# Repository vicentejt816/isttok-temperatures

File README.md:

# isttok-temperatures
projeto para medir temperaturas no tokamak ISTTOK

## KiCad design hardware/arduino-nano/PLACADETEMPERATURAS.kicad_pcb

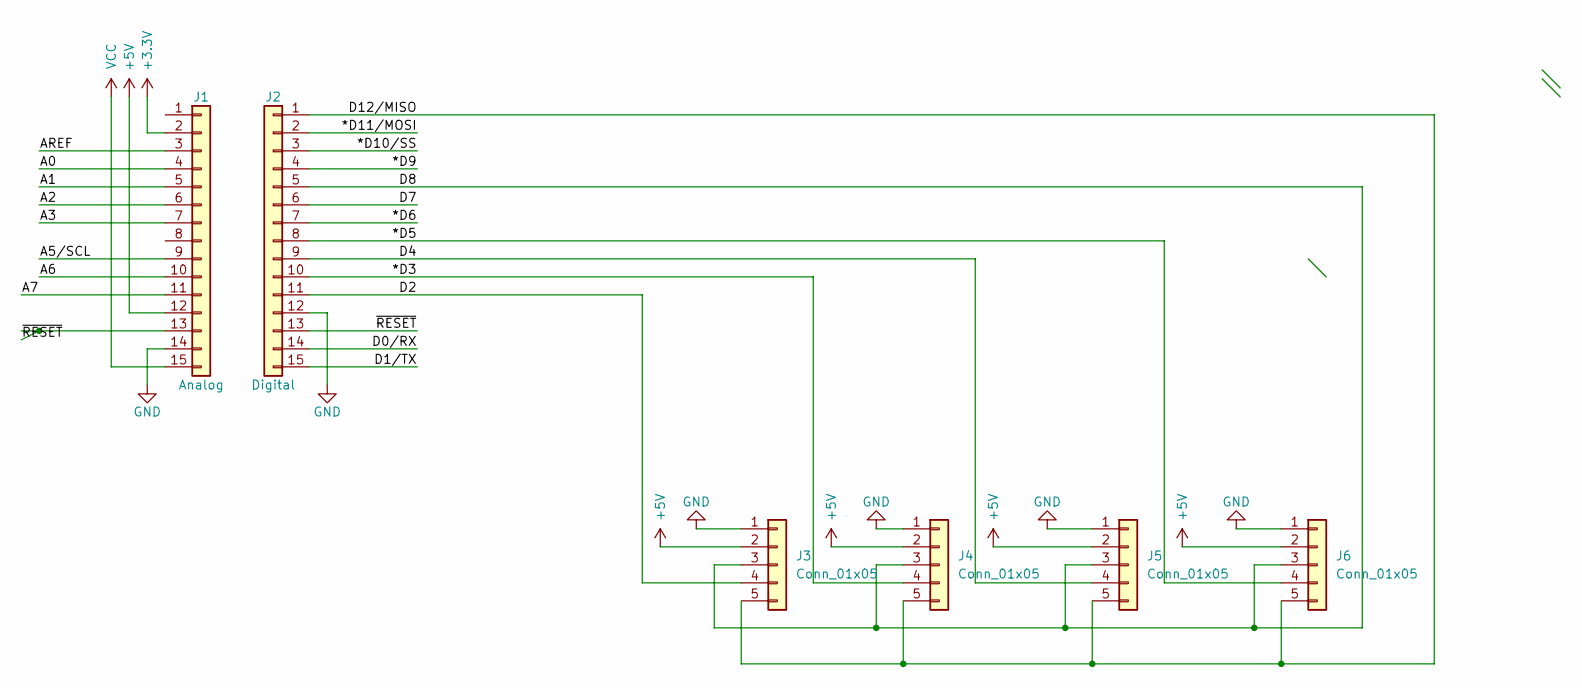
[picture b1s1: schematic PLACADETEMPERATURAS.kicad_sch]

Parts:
J1: Analog; PinHeader_1x15_P2.54mm_Vertical
J2: Digital; PinHeader_1x15_P2.54mm_Vertical
J3, J4, J5, J6: Conn_01x05; PinHeader_1x05_P2.54mm_Vertical

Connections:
+3V3: J1.2
+5V: J1.12, J3.2, J4.2, J5.2, J6.2
/*D3: J2.10, J4.4
/*D5: J2.8, J6.4
/*D6: J2.7
/*D9: J2.4
/*D10/SS: J2.3
/*D11/MOSI: J2.2
/A0: J1.4
/A1: J1.5
/A2: J1.6
/A3: J1.7
/A5/SCL: J1.9
/A6: J1.10
/A7: J1.11
/AREF: J1.3
/D0/RX: J2.14
/D1/TX: J2.15
/D2: J2.11, J3.4
/D4: J2.9, J5.4
/D7: J2.6
/D8: J2.5, J3.3, J4.3, J5.3, J6.3
/D12/MISO: J2.1, J3.5, J4.5, J5.5, J6.5
/~RESET: J1.13, J2.13
GND: J1.14, J2.12, J3.1, J4.1, J5.1, J6.1
VCC: J1.15

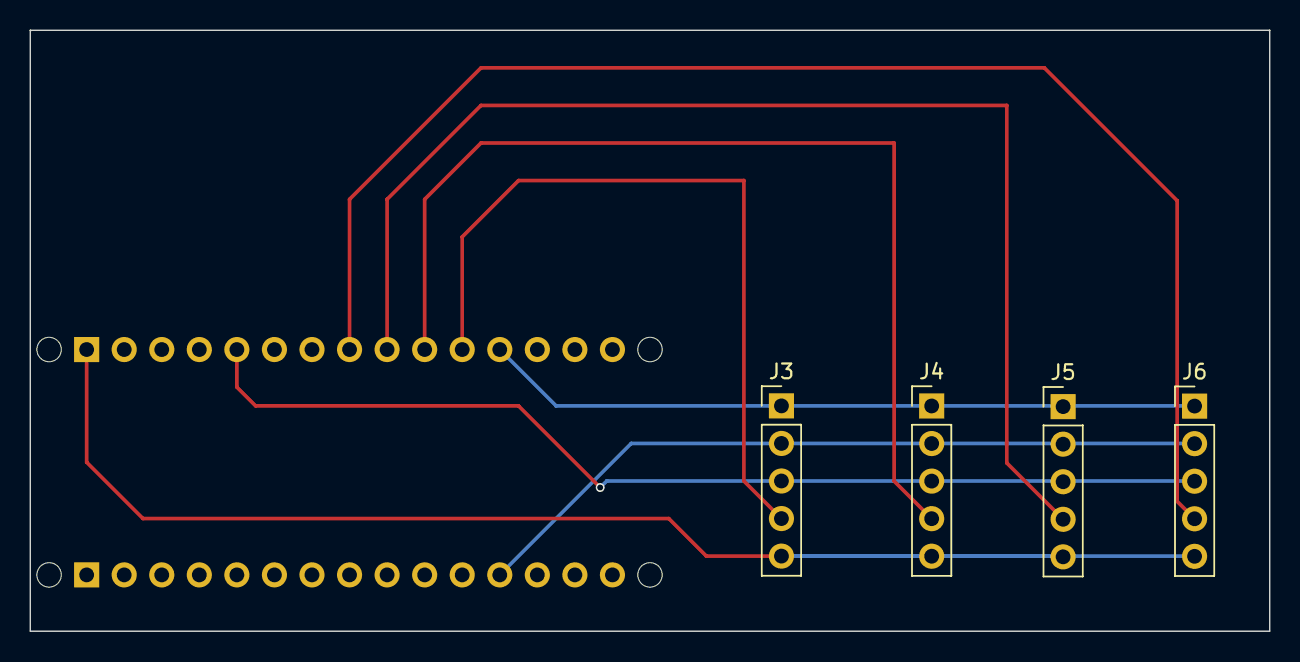
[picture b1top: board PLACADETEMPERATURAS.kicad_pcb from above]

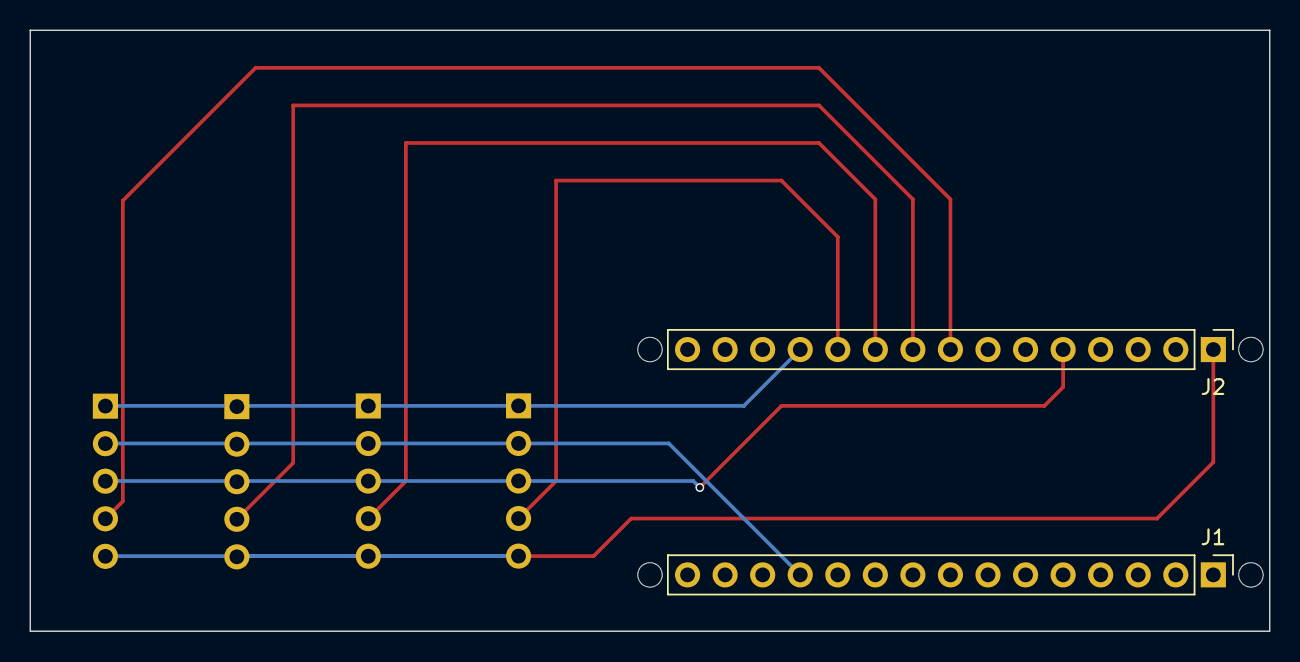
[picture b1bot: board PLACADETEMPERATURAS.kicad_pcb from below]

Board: 2 copper layers, 83.8 x 40.6 mm, 10 parts (2 on the bottom side), 9 nets.

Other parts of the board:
MH1, MH2, MH3, MH4: MountingHole_65mil

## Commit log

2025-06-24 Upload Code
2025-06-24 Upload files
2025-06-26 Actualizacao de Esquematico
